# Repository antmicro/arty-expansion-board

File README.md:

# Antmicro Arty A7 expansion board

Copyright (c) 2019-2023 [Antmicro](https://www.antmicro.com)

## Overview

This project contains open hardware design files for expansion board compatible with Digilent [Arty A7 development platform](https://store.digilentinc.com/arty-a7-artix-7-fpga-development-board-for-makers-and-hobbyists/).
The expansion board utilizes a set of PMOD connectors on Arty board to provide additional IO interfaces.

## Project structure

The main directory contains the KiCAD design files, LICENSE and README.
The remaining files are stored in the following directories:

* ``3d-model`` -  contains mechanical model of the board
* ``lib`` - contains the component libraries
* ``doc`` - contains selected files for device fabrication (schematic in PDF, BoM)
* ``img`` - contains graphics for this README

## Key features

* HDMI connector
* microSD card connector
* USB 2.0 host controller implemented with Maxim [MAX3421EEHJ](https://datasheets.maximintegrated.com/en/ds/MAX3421E.pdf)
* Analog audio output implemented with Cirrus Logic [CS4344](https://www.cirrus.com/products/cs4344-45-48) D/A converter
* Analog (line) audio input implemented with Cirrus Logic [CS5343](https://www.cirrus.com/products/cs5343-44) A/D converter
* GPIO expander with LED indicators

## License

This project is licensed under the [Apache-2.0 ](LICENSE) license.

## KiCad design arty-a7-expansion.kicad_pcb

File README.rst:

================================
Antmicro Arty A7 expansion board
================================

Copyright (c) 2019-2021 `Antmicro <https://www.antmicro.com>`_

.. figure:: img/expansion-board.png

Overview
========

This repository contains open hardware design files for expansion board compatible with Digilent `Arty A7 development platform <https://store.digilentinc.com/arty-a7-artix-7-fpga-development-board-for-makers-and-hobbyists/>`_.
The expansion board utilizes a set of PMOD connectors on Arty board to provide additional IO interfaces.

Repository structure
====================

The main repository directory contains the KiCAD design files, LICENSE and README.
The remaining files are stored in the following directories:

* ``3d-model`` -  contains mechanical model of the board
* ``lib`` - contains the component libraries
* ``doc`` - contains selected files for device fabrication (schematic in PDF, BoM)
* ``img`` - contains graphics for this README

Key features
============

* HDMI connector
* microSD card connector
* USB 2.0 host controller implemented with Maxim `MAX3421EEHJ <https://datasheets.maximintegrated.com/en/ds/MAX3421E.pdf>`_
* Analog audio output implemented with Cirrus Logic `CS4344 <https://www.cirrus.com/products/cs4344-45-48/>`_ D/A converter
* Analog (line) audio input implemented with Cirrus Logic `CS5343 <https://www.cirrus.com/products/cs5343-44/>`_ A/D converter
* GPIO expander with LED indicators

License
=======

`Apache-2.0 <LICENSE>`_

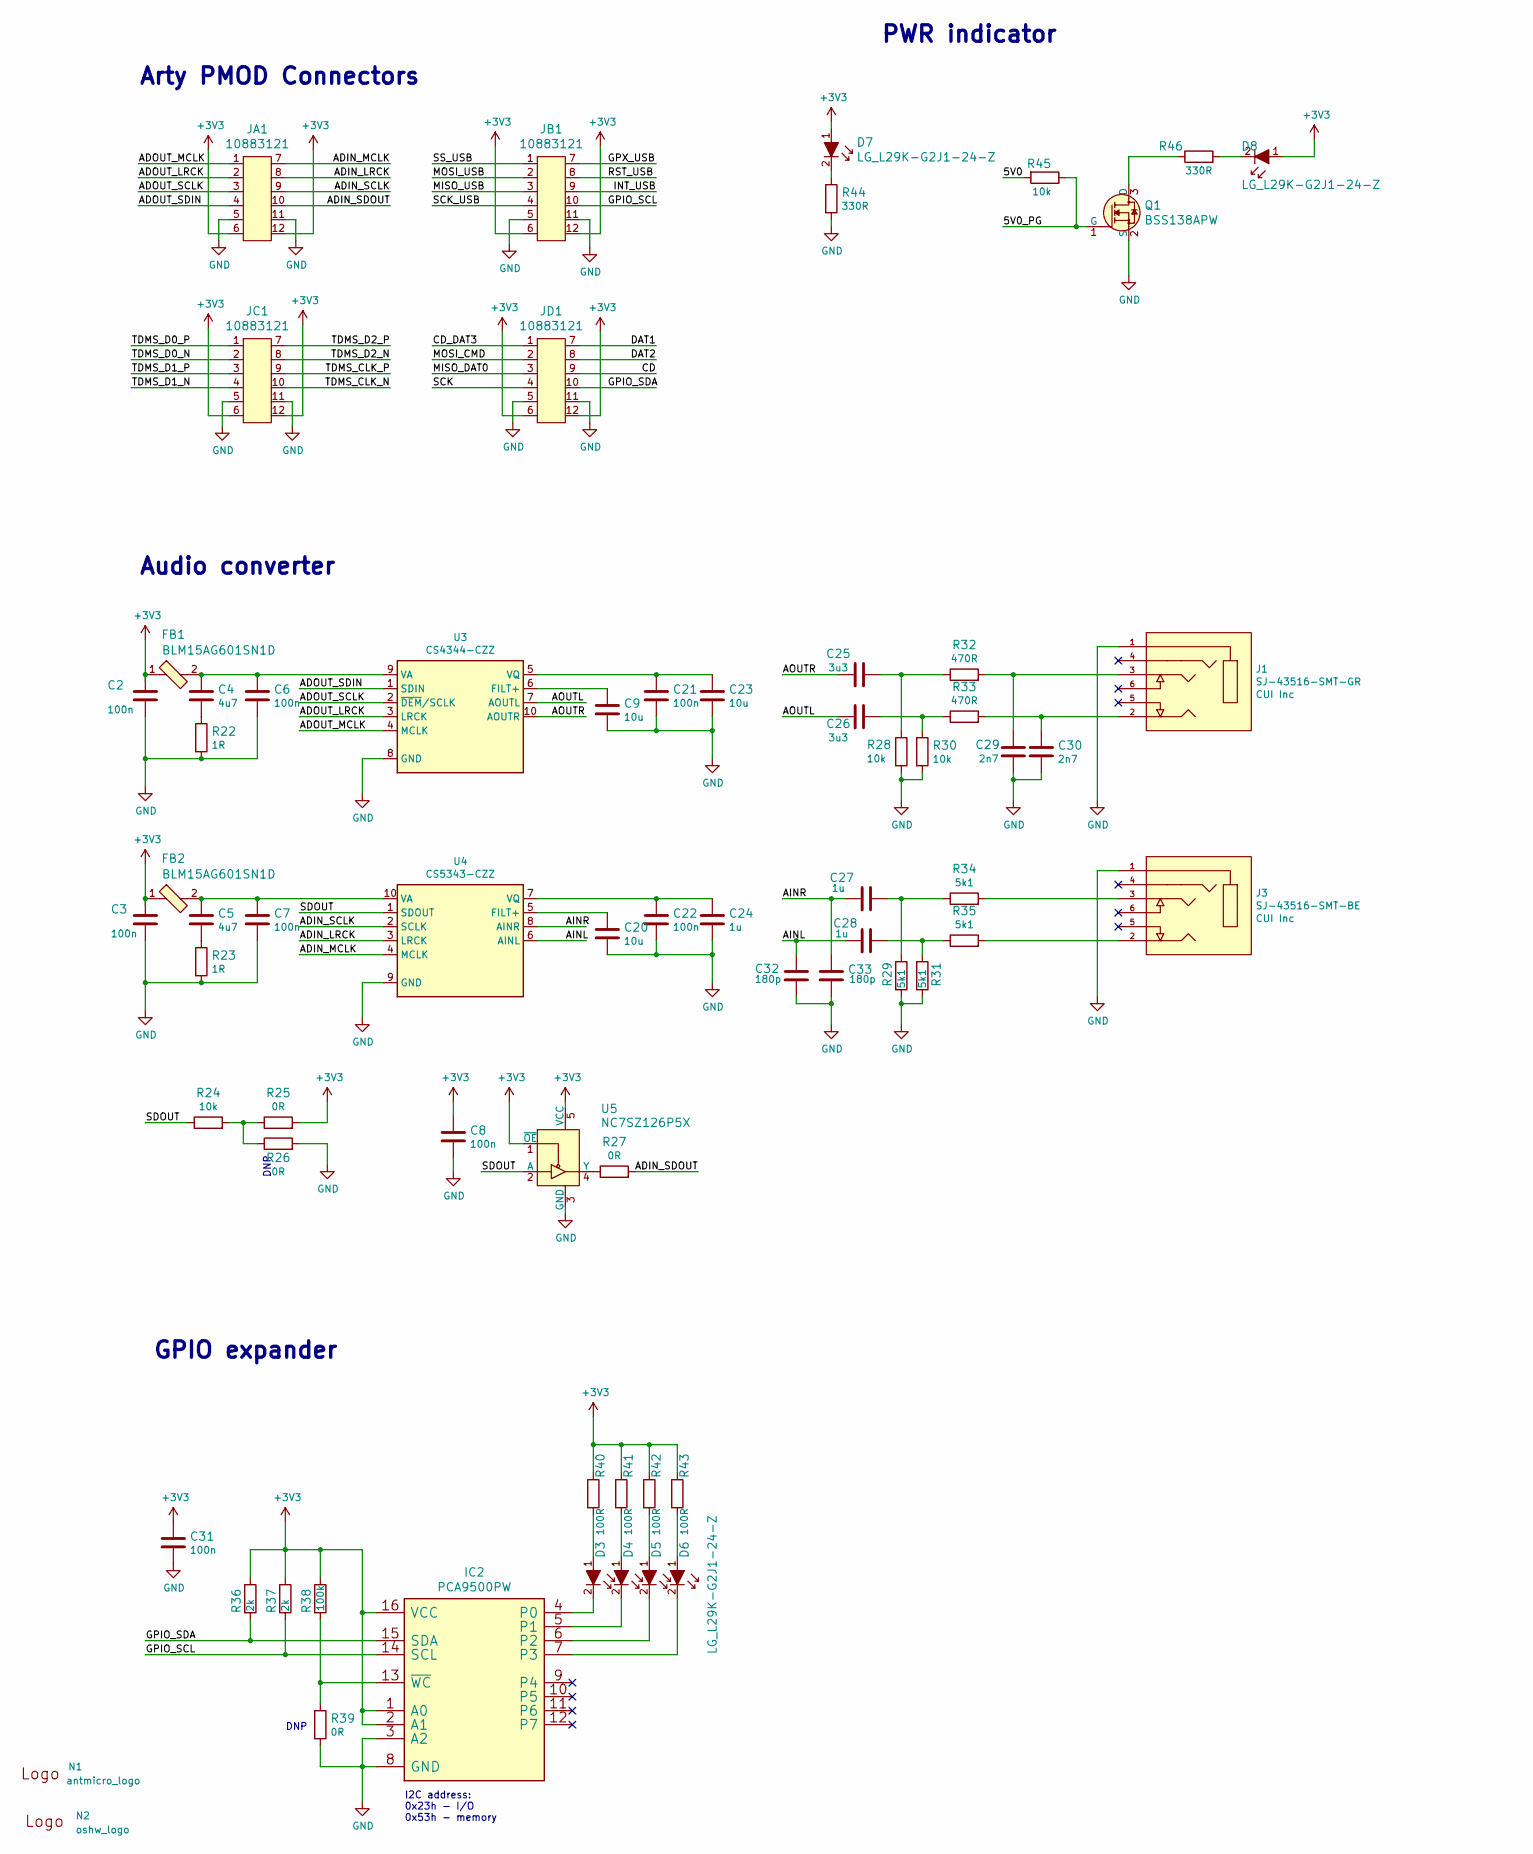
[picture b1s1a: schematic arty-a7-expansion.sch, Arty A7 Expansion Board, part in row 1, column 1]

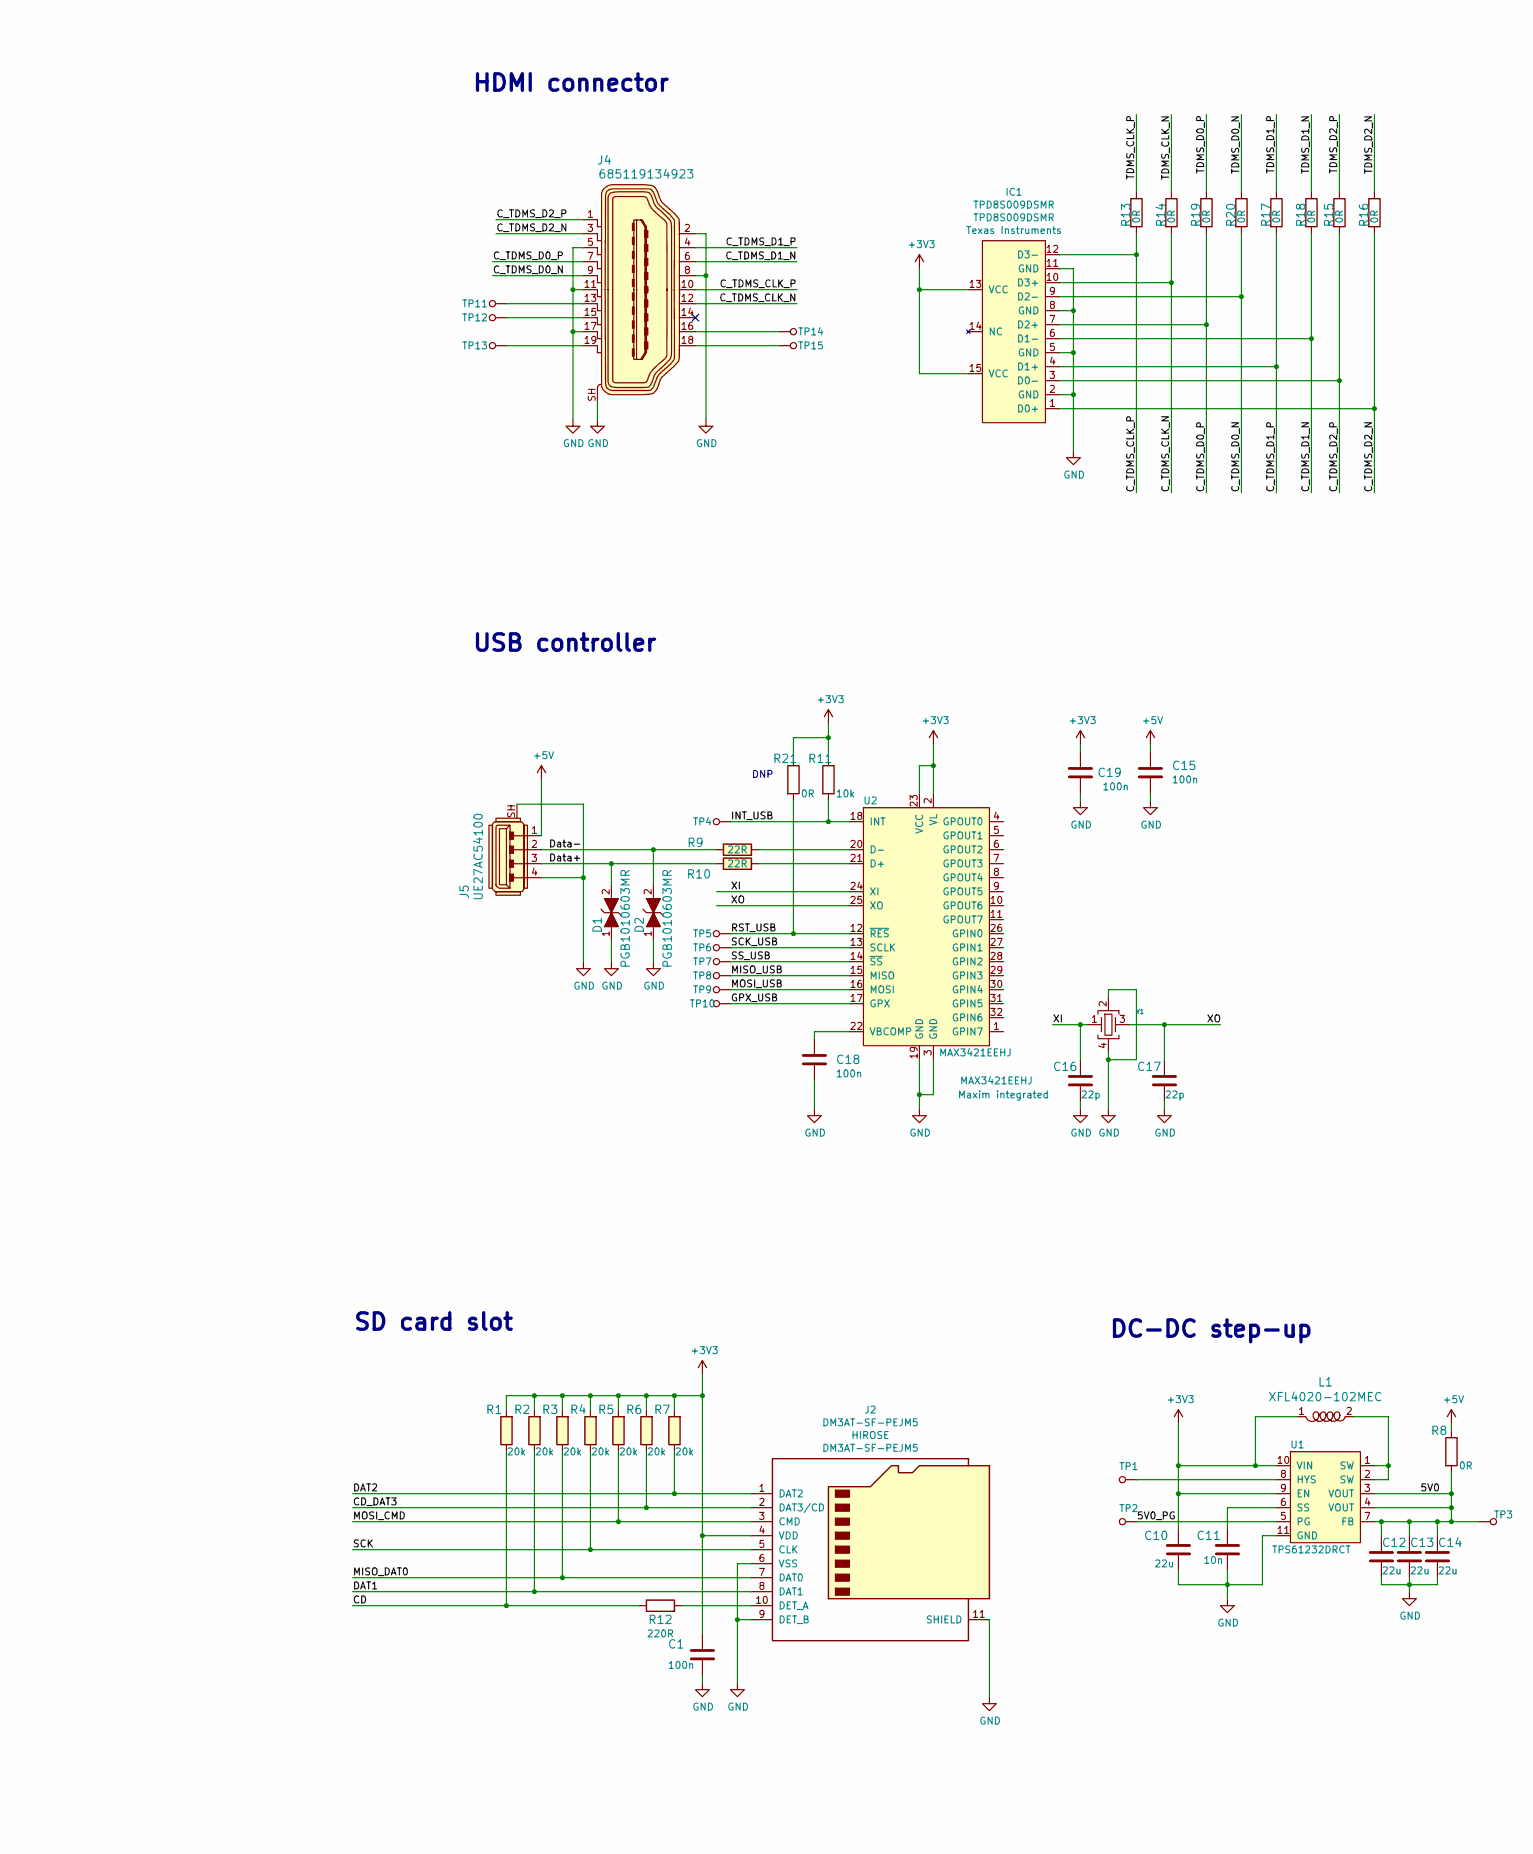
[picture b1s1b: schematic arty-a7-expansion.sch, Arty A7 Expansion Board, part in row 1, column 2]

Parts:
C1, C15, C18, C19, C31: C_100n_0402_6V3; 0402-cap; MPN 0402X104K6R3CT
C2, C3, C6, C7, C8, C21, C22: C_100n_0402_16V; 0402-cap; MPN MC0402B104K160CT
C4, C5: C_4u7_0402; 0402-cap; MPN GRM155R61A475MEAAD
C9, C20, C23: C_10u_0402; 0402-cap; MPN C1005X5R0J106M050BC
C10, C12, C13, C14: C_22u_0603; 0603-cap; MPN GRM188R60J226MEA0D
C11: C_10n_0402; 0402-cap; MPN 04025G103ZAT2A
C16, C17: C_22p_0402; 0402-cap; MPN CC0402JRNPO9BN220
C24, C27, C28: C_1u_0402; 0402-cap; MPN C1005X6S1A105K050BC
C25, C26: C_3u3_0603; 0603-cap; MPN C0603C335M9PACTU
C29, C30: C_2n7_0603; 0603-cap; MPN C0603C272K5RACTU
C32, C33: C_180p_0402; 0402-cap; MPN 04025A181JAT2A
D1, D2: PGB1010603MR; MPN PGB1010603MR
D3, D4, D5, D6, D7, D8: LG_L29K-G2J1-24-Z; LED_0603; MPN LG L29K-G2J1-24-Z
FB1, FB2: BLM15AG601SN1D; 0402-res; MPN BLM15AG601SN1D
IC1: TPD8S009DSMR; R-PDSO-N15; MPN TPD8S009DSMR
IC2: PCA9500PW; TSSOP-16; MPN PCA9500PW
J1: SJ-43516-SMT-GR; CUI_SJ-43516-SMT-GR; MPN SJ-43516-SMT-GR
J2: DM3AT-SF-PEJM5; MicroSD_DM3AT-SF-PEJM5; MPN DM3AT-SF-PEJM5
J3: SJ-43516-SMT-BE; CUI_SJ-43516-SMT-BE; MPN SJ-43516-SMT-BE
J4: 685119134923; HDMI_A_Female_685119134923; MPN 685119134923
J5: UE27AC54100; USB_A_Female_UE27AC54100; MPN UE27AC54100
JA1: 10883121; PinHeader_6x2_P2.54mm_Horizontal_Mirrored; MPN 10883121
JB1: 10883121; PinHeader_6x2_P2.54mm_Horizontal_Mirrored; MPN 10883121
JC1: 10883121; PinHeader_6x2_P2.54mm_Horizontal_Mirrored; MPN 10883121
JD1: 10883121; PinHeader_6x2_P2.54mm_Horizontal_Mirrored; MPN 10883121
L1: XFL4020-102MEC; XFL4020-102MEB; MPN XFL4020-102MEC
N1: antmicro_logo; antmicro-logo_scaled_30mm
N2: oshw_logo; oshw-logo
Q1: BSS138APW; SC70-3; MPN BSS138PW
R1, R2, R3, R4, R5, R6, R7: R_20k_0402; 0402-res; MPN CRCW040220K0FKED
R8, R13, R14, R15, R16, R17, R18, R19, R20, R21, R25, R26, R27, R39: R_0R_0402; 0402-res; MPN ERJ2GE0R00X
R9, R10: R_22R_0402; 0402-res; MPN CRCW040222R0FKED
R11, R24, R28, R30, R45: R_10k_0402; 0402-res; MPN CRCW040210K0FKEDHP
R12: R_220R_0402; 0402-res; MPN ERJ2GEJ221X
R22, R23: R_1R_0402; 0402-res; MPN RC0402FR-071RL
R29, R31, R34, R35: R_5k1_0603; 0603-res; MPN CRCW06035K10FKEA
R32, R33: R_470R_0402; 0402-res; MPN CRCW0402470RFKED.
R36, R37: R_2k_0402; 0402-res; MPN CRCW04022K00FKED
R38: R_100k_0402; 0402-res; MPN CRCW0402100KFKEDHP
R40, R41, R42, R43: R_100R_0402; 0402-res; MPN CR0402-FX-1000GLF
R44, R46: R_330R_0402; 0402-res; MPN MCMR04X3300FTL
TP1, TP2, TP3, TP4, TP5, TP6, TP7, TP8, TP9, TP10, TP11, TP12, TP13, TP14, TP15: TP_SMD1MM; Testpoint_smd_1mm
U1: TPS61232DRCT; VSON-10-1EP_3x3mm; MPN TPS61232DRCT
U2: MAX3421EEHJ; TQFP-32_5x5mm; MPN MAX3421EEHJ
U3: CS4344-CZZ; 10TSSOP; MPN CS4344-CZZ
U4: CS5343-CZZ; 10TSSOP; MPN CS5343-CZZ
U5: NC7SZ126P5X; SC-70-5; MPN NC7SZ126P5X
Y1: ABM8G-12.000MHZ-18-D2Y-T; KX-7; MPN ABM8G-12.000MHZ-18-D2Y-T

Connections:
+3V3: C1.1, C2.1, C3.1, C8.1, C10.1, C19.2, C31.2, D7.1, D8.1, FB1.1, FB2.1, IC1.13 (VCC), IC1.15 (VCC), IC2.1 (A0), IC2.2 (A1), IC2.16 (VCC), J2.4 (VDD), JA1.6, JA1.12, JB1.6, JB1.12, JC1.6, JC1.12, JD1.6, JD1.12, L1.1, R1.2, R2.2, R3.2, R4.2, R5.2, R6.2, R7.2, R11.1, R21.1, R25.2, R36.1, R37.1, R38.1, R40.1, R41.1, R42.1, R43.1, U1.9 (EN), U1.10 (VIN), U2.2 (VL), U2.23 (VCC), U5.1 (~OE), U5.5 (VCC)
+5V: C15.1, J5.1, R8.1
/5V0: C12.1, C13.1, C14.1, R8.2, R45.2, TP3.1, U1.3 (VOUT), U1.4 (VOUT), U1.7 (FB)
/5V0_PG: Q1.1 (G), R45.1, TP2.1, U1.5 (PG)
/ADIN_LRCK: JA1.8, U4.3 (LRCK)
/ADIN_MCLK: JA1.7, U4.4 (MCLK)
/ADIN_SCLK: JA1.9, U4.2 (SCLK)
/ADIN_SDOUT: JA1.10, R27.2
/ADOUT_LRCK: JA1.2, U3.3 (LRCK)
/ADOUT_MCLK: JA1.1, U3.4 (MCLK)
/ADOUT_SCLK: JA1.3, U3.2 (~DEM~/SCLK)
/ADOUT_SDIN: JA1.4, U3.1 (SDIN)
/AINL: C28.2, C32.2, U4.6 (AINL)
/AINR: C27.2, C33.2, U4.8 (AINR)
/AOUTL: C26.2, U3.7 (AOUTL)
/AOUTR: C25.2, U3.10 (AOUTR)
/CD: JD1.9, R1.1, R12.1
/CD_DAT3: J2.2 (DAT3/CD), JD1.1, R6.1
/C_TDMS_CLK_N: IC1.10 (D3+), J4.12, R14.2
/C_TDMS_CLK_P: IC1.12 (D3-), J4.10, R13.2
/C_TDMS_D0_N: IC1.9 (D2-), J4.9, R20.2
/C_TDMS_D0_P: IC1.7 (D2+), J4.7, R19.2
/C_TDMS_D1_N: IC1.6 (D1-), J4.6, R18.2
/C_TDMS_D1_P: IC1.4 (D1+), J4.4, R17.2
/C_TDMS_D2_N: IC1.1 (D0+), J4.3, R16.2
/C_TDMS_D2_P: IC1.3 (D0-), J4.1, R15.2
/DAT1: J2.8 (DAT1), JD1.7, R2.1
/DAT2: J2.1 (DAT2), JD1.8, R7.1
/Data+: D1.2, J5.3, R10.1
/Data-: D2.2, J5.2, R9.1
/GPIO_SCL: IC2.14 (SCL), JB1.10, R37.2
/GPIO_SDA: IC2.15 (SDA), JD1.10, R36.2
/GPX_USB: JB1.7, TP10.1, U2.17 (GPX)
/INT_USB: JB1.9, R11.2, TP4.1, U2.18 (INT)
/MISO_DAT0: J2.7 (DAT0), JD1.3, R3.1
/MISO_USB: JB1.3, TP8.1, U2.15 (MISO)
/MOSI_CMD: J2.3 (CMD), JD1.2, R5.1
/MOSI_USB: JB1.2, TP9.1, U2.16 (MOSI)
/RST_USB: JB1.8, R21.2, TP5.1, U2.12 (~RES)
/SCK: J2.5 (CLK), JD1.4, R4.1
/SCK_USB: JB1.4, TP6.1, U2.13 (SCLK)
/SDOUT: R24.1, U4.1 (SDOUT), U5.2 (A)
/SS_USB: JB1.1, TP7.1, U2.14 (~SS)
/TDMS_CLK_N: JC1.10, R14.1
/TDMS_CLK_P: JC1.9, R13.1
/TDMS_D0_N: JC1.2, R20.1
/TDMS_D0_P: JC1.1, R19.1
/TDMS_D1_N: JC1.4, R18.1
/TDMS_D1_P: JC1.3, R17.1
/TDMS_D2_N: JC1.8, R16.1
/TDMS_D2_P: JC1.7, R15.1
/XI: C16.1, U2.24 (XI), Y1.1
/XO: C17.1, U2.25 (XO), Y1.3
GND: C1.2, C2.2, C3.2, C6.2, C7.2, C8.2, C9.2, C10.2, C11.2, C12.2, C13.2, C14.2, C15.2, C16.2, C17.2, C18.2, C19.1, C20.2, C21.2, C22.2, C23.2, C24.2, C29.2, C30.2, C31.1, C32.1, C33.1, D1.1, D2.1, IC1.2 (GND), IC1.5 (GND), IC1.8 (GND), IC1.11 (GND), IC2.3 (A2), IC2.8 (GND), J1.1, J2.6 (VSS), J2.9 (DET_B), J2.11 (SHIELD), J3.1, J4.2, J4.5, J4.8, J4.11, J4.17, J4.SH, J5.4, J5.SH, JA1.5, JA1.11, JB1.5, JB1.11, JC1.5, JC1.11, JD1.5, JD1.11, Q1.2 (S), R22.2, R23.2, R26.2, R28.2, R29.2, R30.2, R31.2, R39.2, R44.2, U1.11 (GND), U2.3 (GND), U2.19 (GND), U3.8 (GND), U4.9 (GND), U5.3 (GND), Y1.2, Y1.4
unnamed: C4.1, C6.1, FB1.2, U3.9 (VA)
unnamed: C4.2, R22.1
unnamed: C5.1, C7.1, FB2.2, U4.10 (VA)
unnamed: C5.2, R23.1
unnamed: C9.1, U3.6 (FILT+)
unnamed: C11.1, U1.6 (SS)
unnamed: C18.1, U2.22 (VBCOMP)
unnamed: C20.1, U4.5 (FILT+)
unnamed: C21.1, C23.1, U3.5 (VQ)
unnamed: C22.1, C24.1, U4.7 (VQ)
unnamed: C25.1, R28.1, R32.1
unnamed: C26.1, R30.1, R33.1
unnamed: C27.1, R29.1, R34.1
unnamed: C28.1, R31.1, R35.1
unnamed: C29.1, J1.3, R32.2
unnamed: C30.1, J1.2, R33.2
unnamed: D3.1, R40.2
unnamed: D3.2, IC2.4 (P0)
unnamed: D4.1, R41.2
unnamed: D4.2, IC2.5 (P1)
unnamed: D5.1, R42.2
unnamed: D5.2, IC2.6 (P2)
unnamed: D6.1, R43.2
unnamed: D6.2, IC2.7 (P3)
unnamed: D7.2, R44.1
unnamed: D8.2, R46.2
unnamed: IC2.13 (~WC), R38.2, R39.1
unnamed: J2.10 (DET_A), R12.2
unnamed: J3.2, R35.2
unnamed: J3.3, R34.2
unnamed: J4.13, TP11.1
unnamed: J4.15, TP12.1
unnamed: J4.16, TP14.1
unnamed: J4.18, TP15.1
unnamed: J4.19, TP13.1
unnamed: L1.2, U1.1 (SW), U1.2 (SW)
unnamed: Q1.3 (D), R46.1
unnamed: R9.2, U2.20 (D-)
unnamed: R10.2, U2.21 (D+)
unnamed: R24.2, R25.1, R26.1
unnamed: R27.1, U5.4 (Y)
unnamed: TP1.1, U1.8 (HYS)

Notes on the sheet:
Arty PMOD Connectors
HDMI connector
SD card slot
DC-DC step-up
USB controller
DNP
Audio converter
GPIO expander
I2C address: 0x23h - I/O 0x53h - memory
PWR indicator

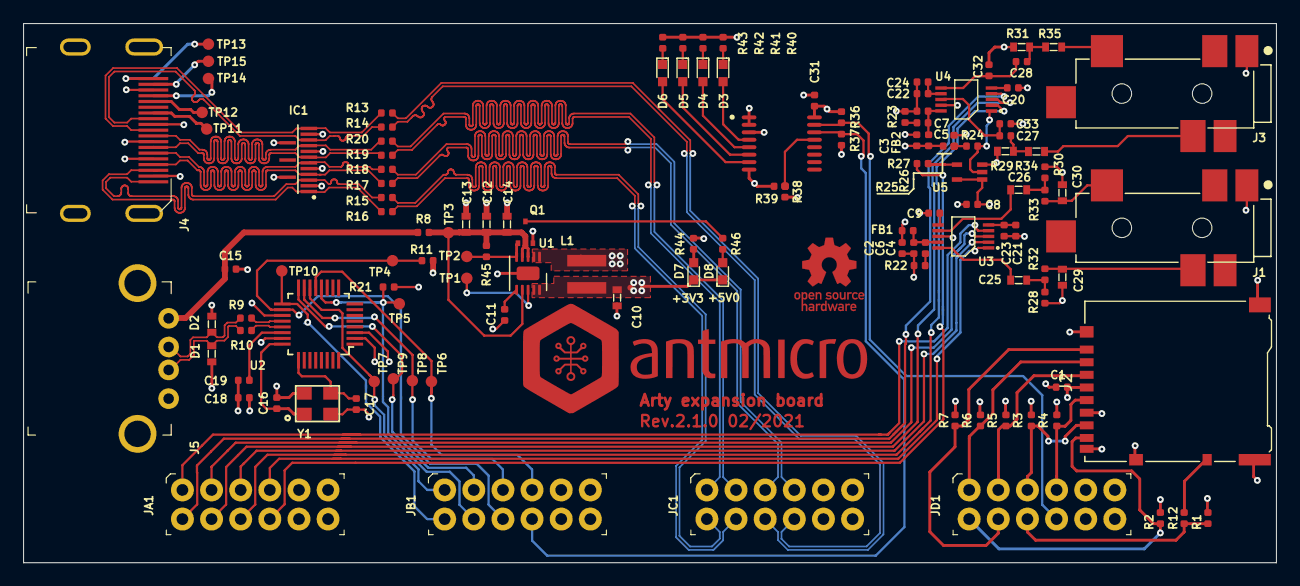
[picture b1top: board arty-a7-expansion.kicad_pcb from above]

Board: 4 copper layers, 109.2 x 47.0 mm, 125 parts (0 on the bottom side), 96 nets.

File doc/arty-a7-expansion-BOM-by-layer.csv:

Reference,Quantity,Value,Footprint,Manufacturer,MPN,Layer,
C1 C15 C18 C19 C31,5,C_100n_0402_6V3,0402-cap,Walsin,0402X104K6R3CT,Top,
C10 C12 C13 C14,4,C_22u_0603,0603-cap,MURATA,GRM188R60J226MEA0D,Top,
C11,1,C_10n_0402,0402-cap,AVX,04025G103ZAT2A,Top,
C16 C17,2,C_22p_0402,0402-cap,YAGEO,CC0402JRNPO9BN220,Top,
C2 C3 C6 C7 C8 C21 C22,7,C_100n_0402_16V,0402-cap,MULTICOMP,MC0402B104K160CT,Top,
C24 C27 C28,3,C_1u_0402,0402-cap,TDK,C1005X6S1A105K050BC,Top,
C25 C26,2,C_3u3_0603,0603-cap,KEMET,C0603C335M9PACTU,Top,
C29 C30,2,C_2n7_0603,0603-cap,KEMET,C0603C272K5RACTU,Top,
C32 C33,2,C_180p_0402,0402-cap,AVX,04025A181JAT2A,Top,
C4 C5,2,C_4u7_0402,0402-cap,MURATA,GRM155R61A475MEAAD,Top,
C9 C20 C23,3,C_10u_0402,0402-cap,MURATA,GRM155R60J106ME44D,Top,
D1 D2,2,PGB1010603MR,PGB1010603MR,Littelfuse Inc.,PGB1010603MR,Top,
D3 D4 D5 D6,4,LG_L29K-G2J1-24-Z,LED_0603,OSRAM Opto Semiconductors Inc.,LG L29K-G2J1-24-Z,Top,
FB1 FB2,2,BLM15AG601SN1D,0402-res,Murata,BLM15AG601SN1D,Top,
IC1,1,TPD8S009DSMR,R-PDSO-N15,Texas Instruments,TPD8S009DSMR,Top,
IC2,1,PCA9500PW,TSSOP-16,NXP,PCA9500PW,Top,
J1,1,SJ-43516-SMT-GR,CUI_SJ-43516-SMT-GR,CUI Inc,SJ-43516-SMT-GR,Top,
J2,1,1140084168,MicroSD_1140084168,Amphenol,1140084168,Top,
J3,1,SJ-43516-SMT-BE,CUI_SJ-43516-SMT-BE,CUI Inc,SJ-43516-SMT-BE,Top,
J4,1,685119134923,HDMI_A_Female_685119134923,Amphenol,685119134923,Top,
J5,1,UE27AC54100,USB_A_Female_UE27AC54100,Amphenol ICC (Commercial Products),UE27AC54100,Top,
JA1 JB1 JC1 JD1,4,10883121,PinHeader_6x2_P2.54mm_Horizontal_Mirrored,Molex,10883121,Top,
L1,1,XFL4020-102MEC,XFL4020-102MEB,Coilcraft,XFL4020-102MEC,Top,
R1 R2 R3 R4 R5 R6 R7,7,R_20k_0402,0402-res,VISHAY,CRCW040220K0FKED,Top,
R11 R24 R28 R30,4,R_10k_0402,0402-res,VISHAY,CRCW040210K0FKEDHP,Top,
R12,1,R_220R_0402,0402-res,Panasonic,ERJ2GEJ221X,Top,
R22 R23,2,R_1R_0402,0402-res,YAGEO,RC0402FR-071RL,Top,
R29 R31 R34 R35,4,R_5k1_0603,0603-res,Vishay,CRCW06035K10FKEA,Top,
R32 R33,2,R_470R_0402,0402-res,VISHAY,CRCW0402470RFKED,Top,
R36 R37,2,R_2k_0402,0402-res,VISHAY,CRCW04022K00FKED,Top,
R38,1,R_100k_0402,0402-res,VISHAY,CRCW0402100KFKEDHP,Top,
R40 R41 R42 R43,4,R_100R_0402,0402-res,BOURNS,CR0402-FX-1000GLF,Top,
R8 R13 R14 R15 R16 R17 R18 R19 R20 R25 R27,11,R_0R_0402,0402-res,PANASONIC,ERJ2GE0R00X,Top,
R9 R10,2,R_22R_0402,0402-res,VISHAY,CRCW040222R0FKED,Top,
U1,1,TPS61232DRCT,VSON-10-1EP_3x3mm,Texas Instruments,TPS61232DRCT,Top,
U2,1,MAX3421EEHJ,TQFP-32_5x5mm,Maxim integrated,MAX3421EEHJ,Top,
U3,1,CS4344-CZZ,10TSSOP,Cirrus Logic,CS4344-CZZ,Top,
U4,1,CS5343-CZZ,10TSSOP,Cirrus Logic,CS5343-CZZ,Top,
U5,1,NC7SZ126P5X,SC-70-5,ON Semiconductor,NC7SZ126P5X,Top,
Y1,1,ABM8G-12.000MHZ-18-D2Y-T,KX-7,Abracon,ABM8G-12.000MHZ-18-D2Y-T ,Top,
R21 R26 R39,3,R_0R_0402,0402-res,PANASONIC,ERJ2GE0R00X,DNP,
N1,1,antmicro_logo,antmicro-logo_scaled_30mm,,,Virtual,
N2,1,oshw_logo,oshw-logo,,,Virtual,
TP1 TP2 TP3 TP5 TP6 TP7 TP8 TP9 TP10 TP11 TP12 TP13 TP14 TP15,14,TP_SMD1MM,Testpoint_smd_1mm,,,Virtual,
TP4,1,TP_SMD1MM-,Testpoint_smd_1mm,,,Virtual,

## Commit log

2019-08-26 Add readme
2019-08-26 Add schematic file and component placement
    A schematic file and proposed arrangement of elements have been added.
2020-02-13 Replaced HDMI connector
2020-02-13 Review
2020-02-13 Added USB SPI Interface
2020-02-13 Schematic updates
2020-02-13 Added testpads
2020-02-13 Added 3D model of expansion board
2020-02-13 Added logotype, rotated SD card
2020-02-13 Optimized component placement
2020-02-13 PCB routing
2020-02-13 Bug Fix
2020-02-13 Updated PMOD connectors on PCB
2020-02-13 Added more testpads
2020-02-13 Added PDF schematic
2020-02-13 Added TVS
2020-02-13 Changed HDMI connector through hole
2020-02-13 Prepared files for oshw release
2020-02-13 Cleanup
2020-02-13 Introduced schematic sections
2020-02-13 Updated U1 MPN, updated layout around IC1
2020-02-13 Cleanup, added fabrication outputs
2020-02-13 README updates
2020-02-14 Minor changes
2020-02-14 Added pullup resistor to USB_RESET, updated layout
2020-02-17 Added CSV files with BOM and Pick and Place
2020-02-17 Standardize components
2020-02-17 Update mpn
2020-02-17 Update library references
2020-02-17 Update fabrication outputs
2020-07-17 Add revision 2.0.1
2021-02-12 Add PWR indicator
2021-02-12 Corrected silks
2021-02-12 Replace micro SD card connector
2021-02-12 Add 5V0 led indicator
2021-02-12 Bump revision to 2.1.0
2021-02-12 PCB fabrication E1285910
2021-02-12 Update LICENSE
2021-02-12 Update dates in README
2021-02-12 Update documentation
2021-04-22 Specify audio controllers in README
2021-06-24 Notes added by 'git notes add'
2023-03-31 README: change into md
2023-03-31 Update image name
2023-03-31 Clean the images
2023-03-31 README: fix bullet
